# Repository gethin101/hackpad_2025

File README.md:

# Gethin HackPad v1

This repository contains all files for my **AMD x HackClub Macropad** project.  
The macropad is designed for computer shortcuts, python programming, and game controlling.  

It features:
- 3x3 mechanical keys
- 0.91" OLED display
- Powered by a Seeed XIAO RP2040 microcontroller

---

## 📸 Hackpad Overview

This is the overview of my hackpad assembled in Fusion 360 which shows how it should be all put together

Demo video: [link](https://drive.google.com/file/d/1SN6_Jn4tApgLRpyzZipDD-V8Z1X3xwi7/view)

---

## 🔌 Schematic

This is my schematic that I designed in KiCad showing which components I'm using and how they are connected. As you can see, each key switch is wired seperately to the RP2040 and the OLED is orded in GND-VCC-SCL-SDA so that it is compatible with the 0.91" display sent by HackClub

---

## 🖥️ PCB Layout
This is my PCB layout that I designed in the KiCad PCB Designer. It shows all of the component placement and copper wiring so I can visualise all the connections. I also added some customisation on the silkscreen such as a link to this github repository & the name of my Hackpad

---

Build image:

## 🧩 Case Design

I designed the base & cover in Fusion 360 using the measurements from my PCB in KiCad, and I imported all the 3D models in to test-fit all of them together

---

## 📦 Bill of Materials (BOM)
List of all parts used in my hackpad:

| Part | Quantity | Description | 
|------|----------|-------------|
| Mechanical Key Switches | 9 | MX-style switches |
| Cherry Keycaps | 9 | Compatible with MX switches | 
| Seeed XIAO RP2040 | 1 | Microcontroller | 
| OLED Display 0.91" | 1 | I2C interface | 
| PCB | 1 | Double-sided | 
| Case | 1 | 3D printed (prob PLA)| 

---

## Firmware Instructions:

1. Download & install CircuitPython .uf2
2. Connect the Seeed XIAO RP2040 via USB and enter bootloader mode
3. Flash the MCU with the .uf2

Libraries:
1. Download CircuitPython library bundle & unzip
2. Copy displayio, display_text, debouncer & HID to the MCU
3. Upload the `code.py` to the XIAO
4. Test

## 📝 License
This project is open-source under the MIT License and created by @Gethin101

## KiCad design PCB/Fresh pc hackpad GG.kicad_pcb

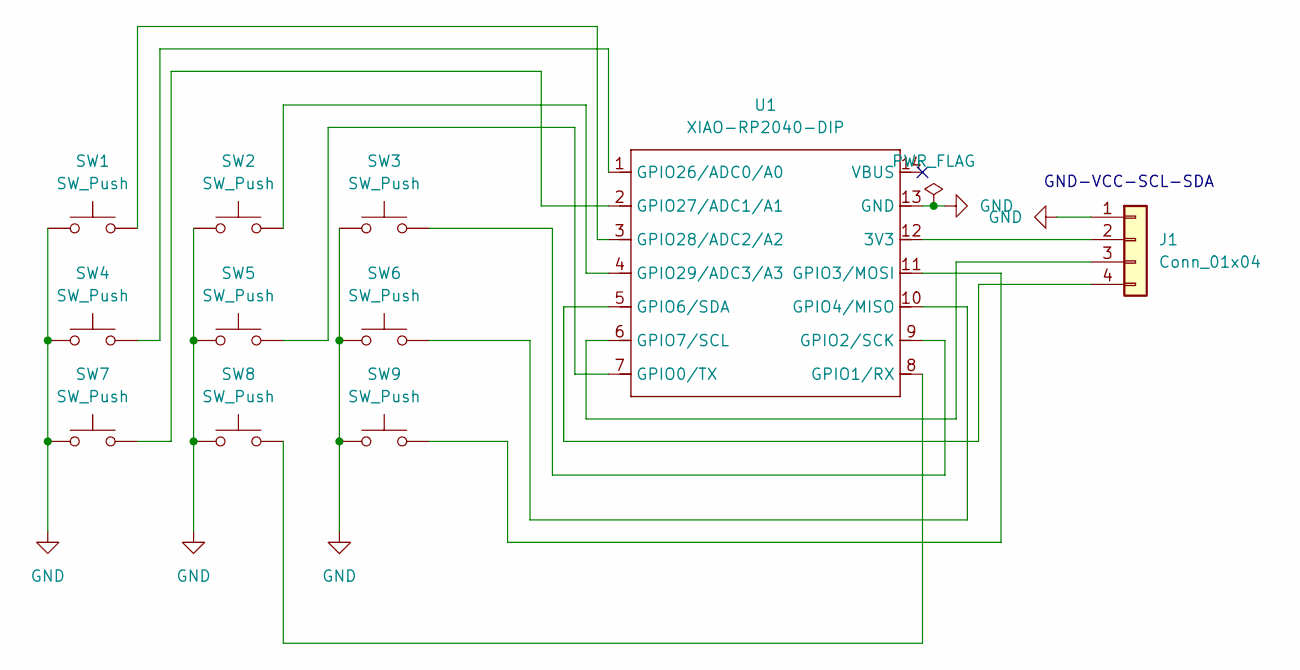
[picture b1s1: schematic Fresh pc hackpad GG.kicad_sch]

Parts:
J1: Conn_01x04; SSD1306-0.91-OLED-4pin-128x32
SW1, SW2, SW3, SW4, SW5, SW6, SW7, SW8, SW9: SW_Push; SW_Cherry_MX_1.00u_PCB
U1: XIAO-RP2040-DIP

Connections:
GND: J1.1, SW1.1, SW2.1, SW3.1, SW4.1, SW5.1, SW6.1, SW7.1, SW8.1, SW9.1, U1.13 (GND)
unnamed: J1.2, U1.12 (3V3)
unnamed: J1.3, U1.6 (GPIO7/SCL)
unnamed: J1.4, U1.5 (GPIO6/SDA)
unnamed: SW5.2, U1.7 (GPIO0/TX)
unnamed: SW8.2, U1.8 (GPIO1/RX)
unnamed: SW3.2, U1.9 (GPIO2/SCK)
unnamed: SW9.2, U1.11 (GPIO3/MOSI)
unnamed: SW6.2, U1.10 (GPIO4/MISO)
unnamed: SW4.2, U1.1 (GPIO26/ADC0/A0)
unnamed: SW7.2, U1.2 (GPIO27/ADC1/A1)
unnamed: SW1.2, U1.3 (GPIO28/ADC2/A2)
unnamed: SW2.2, U1.4 (GPIO29/ADC3/A3)

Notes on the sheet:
GND-VCC-SCL-SDA

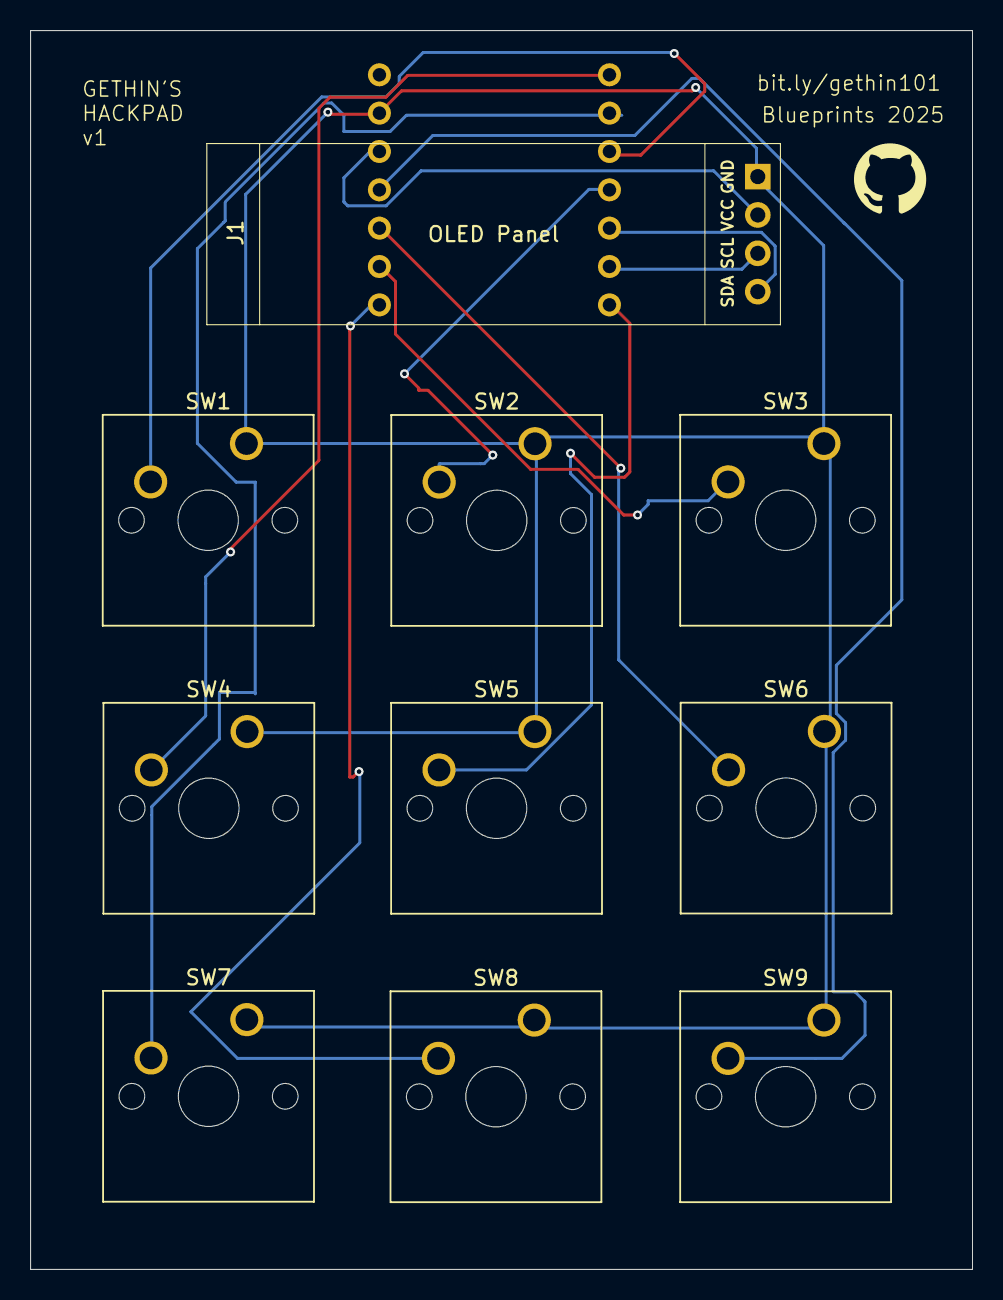
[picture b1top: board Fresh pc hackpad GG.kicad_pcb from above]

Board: 2 copper layers, 62.4 x 82.1 mm, 11 parts (1 on the bottom side), 13 nets.

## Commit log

2025-12-06 Create filler
2025-12-07 Rename Screenshot 2025-12-07 124308.png to hackpad-overview.png
2025-12-07 Rename Screenshot 2025-12-07 124724.png to schematic.png
2025-12-07 Rename Screenshot 2025-12-07 091842.png to pcb.png
2025-12-07 Rename Screenshot 2025-12-07 130254.png to case_cover.png
2025-12-07 Rename Screenshot 2025-12-07 130234.png to case_base.png
2025-12-07 Rename Screenshot 2025-12-07 130637.png to case_assembled_3d.png
2025-12-25 Rename Screenshot 2025-12-24 110527.png to cart1.png
2025-12-25 Rename Screenshot 2025-12-24 110533.png to cart2.png
2025-12-25 Rename Screenshot 2025-12-24 110540.png to cart3.png
2025-12-25 Rename Screenshot 2025-12-24 110545.png to cart4.png
2025-12-25 Rename Screenshot 2025-12-24 110559.png to cart5.png
